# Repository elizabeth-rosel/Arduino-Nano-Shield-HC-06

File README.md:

# HC-06 Module Adapter for Arduino Nano IO Shield

An open-source hardware adapter board to interface the HC-06 Bluetooth module to
the Arduino Nano via an I/O expansion shield.

## About

This was initially made to personally facilitate an logic circuits and design
class, where I condensed the adapter circuit for UART communication between the
HC-06 and the Nano. It is just a simple resistor divider to translate from the
Nano's TX to the HC-06's RX pin, as the HC-06 only operates on 3.3V logic level.

This is a very compact design, designed to be as minimally intrusive on the Nano IO shield as possible. This can also be implemented using a 4x4 perforated prototype board of pitch 2.54mm!

The bottom female pins are designed to slot onto the shield's three-row breakout pins, where the top row is ground, middle is 5V, and bottom rows are data/GPIO.

You may also program other GPIO pins to be the Nano's UART interface, apart from the dedicated ones at PD0 and PD1.

Note: The image shown below is an earlier design prototype.

## List of Materials

| Designator | Footprint / Value                  | Amount |
| ---------- | ---------------------------------- | ------ |
| J1, J2     | 01x02 pin socket with 2.54mm pitch | 2      |
| J3         | 01x04 pin socket with 2.54mm pitch | 1      |
| R1         | 1/4W 2K resistor                   | 1      |
| R2         | 1/4W 1K resistor                   | 1      |

## Assembly

Solder in order of smallest to biggest:

1. R1, R2
2. J1, J2
3. J3

### Notes

- J3 may be substituted with two 01x02 pin sockets with 2.54mm pitch.
- You may use a spare pin header to align the pin sockets correctly when assembling.

## License

This is licensed under the [TAPR Open Hardware License](http://www.tapr.org/OHL).

On the board, this is abbreviated as `TAPR OHL`

© Elizabeth Rosel 2025-2026

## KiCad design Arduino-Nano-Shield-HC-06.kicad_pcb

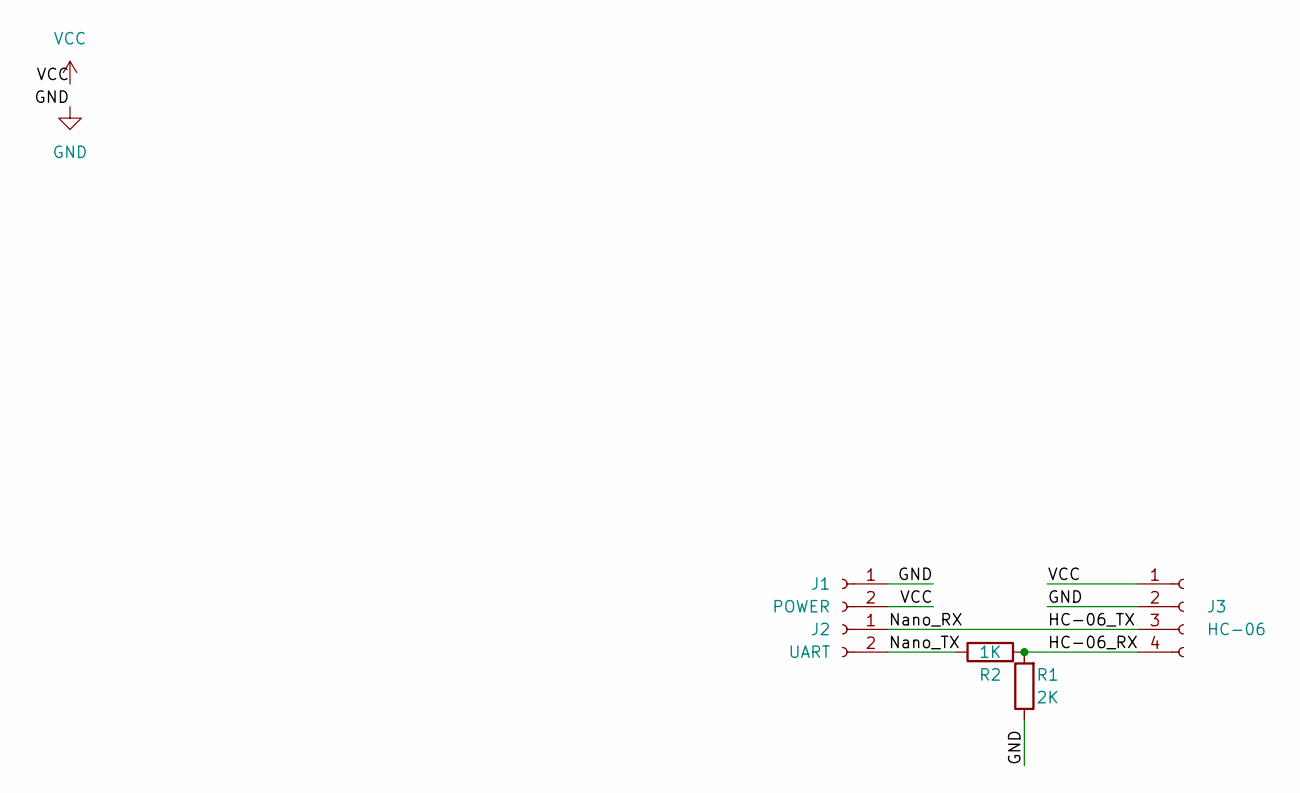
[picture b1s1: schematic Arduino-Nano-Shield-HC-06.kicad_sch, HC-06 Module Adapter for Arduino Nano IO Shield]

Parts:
J1: POWER; PinSocket_1x02_P2.54mm_Vertical
J2: UART; PinSocket_1x02_P2.54mm_Vertical
J3: HC-06; PinSocket_1x04_P2.54mm_Vertical
R1: 2K; R_Axial_DIN0207_L6.3mm_D2.5mm_P2.54mm_Vertical
R2: 1K; R_Axial_DIN0207_L6.3mm_D2.5mm_P2.54mm_Vertical

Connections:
/HC-06_RX: J3.4, R1.2, R2.2
/HC-06_TX: J2.1, J3.3
/Nano_TX: J2.2, R2.1
GND: J1.1, J3.2, R1.1
VCC: J1.2, J3.1

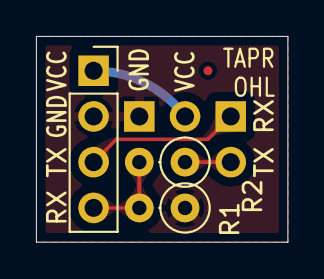
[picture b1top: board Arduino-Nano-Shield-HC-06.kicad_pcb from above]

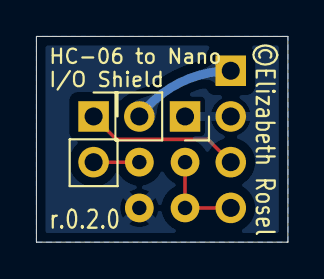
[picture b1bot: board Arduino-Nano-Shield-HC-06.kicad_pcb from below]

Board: 2 copper layers, 14.0 x 11.4 mm, 5 parts (2 on the bottom side), 5 nets.

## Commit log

2026-02-19 Correct abbreviation
2026-02-28 Resize PCB to be smaller
